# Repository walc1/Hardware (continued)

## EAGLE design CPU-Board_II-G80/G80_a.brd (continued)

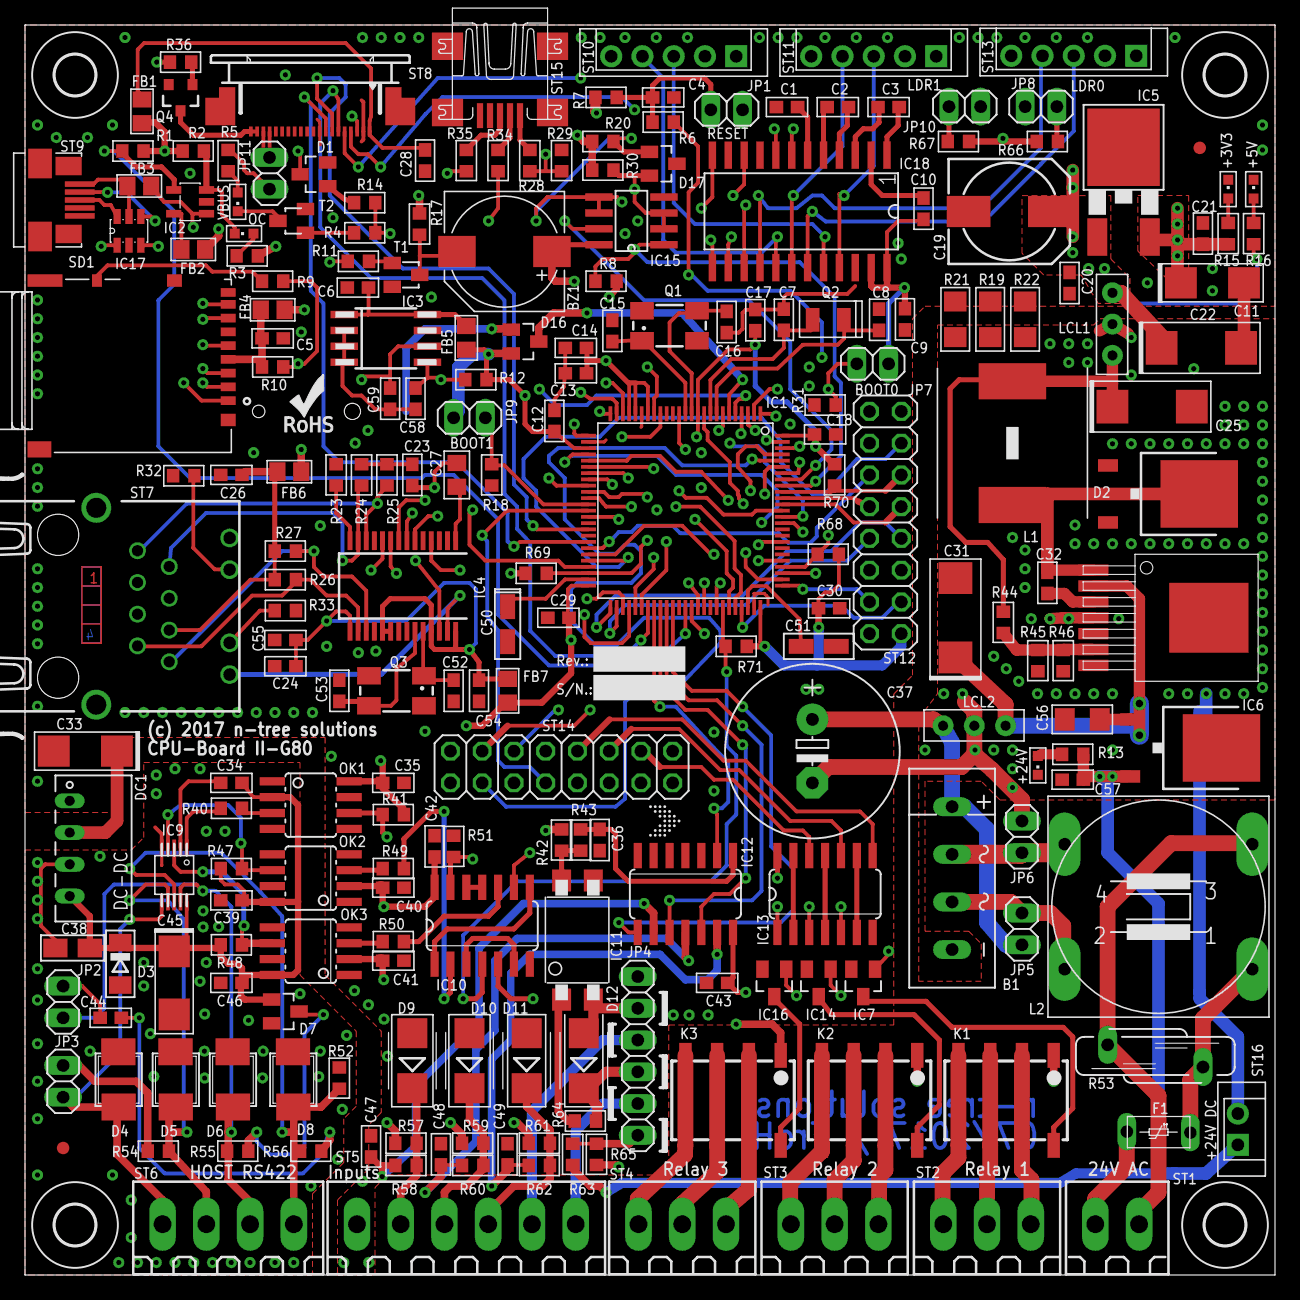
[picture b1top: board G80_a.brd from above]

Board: 4 copper layers, 100.0 x 100.0 mm, 227 parts (1 on the bottom side), 204 nets.

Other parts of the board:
U$1, U$2, U$3, U$4: 3,2

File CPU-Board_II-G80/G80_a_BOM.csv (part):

"Qty";"Value";"Device";"Package";"Parts";"Description";"AVAILABILITY";"DESCRIPTION";"MF";"MP";"MPN";"OC_FARNELL";"OC_NEWARK";"PACKAGE";"PRICE";"PROD_ID";"VALUE";
"7";"";"FERITTE-CHIP-BEAD";"R805";"FB1, FB2, FB3, FB4, FB5, FB6, FB7";"";"";"";"";"";"";"";"";"";"";"";"";
"1";"0,33uF/100V";"C-EUC1206";"C1206";"C56";"CAPACITOR, European symbol";"";"";"";"";"";"";"";"";"";"";"";
"2";"0R";"R-EU_R0603";"R0603";"R63, R65";"RESISTOR, European symbol";"";"";"";"";"";"";"";"";"";"";"";
"3";"0R";"R-EU_R1206";"R1206";"R19, R21, R22";"RESISTOR, European symbol";"";"";"";"";"";"";"";"";"";"";"";
"1";"1000uF/50V";"CPOL-EUE5-13";"E5-13";"C37";"POLARIZED CAPACITOR, European symbol";"";"";"";"";"";"";"";"";"";"";"";
"6";"100R";"R-EU_R0603";"R0603";"R6, R14, R36, R52, R54, R56";"RESISTOR, European symbol";"";"";"";"";"";"";"";"";"";"";"";
"2";"100k";"R-EU_R0603";"R0603";"R7, R55";"RESISTOR, European symbol";"";"";"";"";"";"";"";"";"";"";"";
"36";"100nF";"C-EUC0603";"C0603";"C1, C2, C3, C4, C5, C6, C9, C10, C12, C13, C14, C17, C18, C20, C21, C23, C24, C26, C28, C29, C30, C34, C35, C36, C39, C40, C41, C42, C43, C46, C47, C48, C49, C54, C55, C57";"CAPACITOR, European symbol";"";"";"";"";"";"";"";"";"";"";"";
"2";"100uF/16V lowESR";"CPOL-EUD/7343-31R";"D/7343-31R";"C22, C25";"POLARIZED CAPACITOR, European symbol";"";"";"";"";"";"";"";"";"";"";"";
"25";"10k";"R-EU_R0603";"R0603";"R1, R4, R10, R11, R17, R18, R28, R29, R31, R42, R43, R45, R51, R57, R58, R59, R60, R61, R62, R66, R67, R68, R69, R70, R71";"RESISTOR, European symbol";"";"";"";"";"";"";"";"";"";"";"";
"1";"10nF/100V";"C-EUC0603";"C0603";"C32";"CAPACITOR, European symbol";"";"";"";"";"";"";"";"";"";"";"";
"1";"10nF/50V";"C-EUC0603";"C0603";"C44";"CAPACITOR, European symbol";"";"";"";"";"";"";"";"";"";"";"";
"1";"10uF";"CPOL-EUC/6032-28R";"C/6032-28R";"C11";"POLARIZED CAPACITOR, European symbol";"";"";"";"";"";"";"";"";"";"";"";
"1";"10uF, GRM21BC81E106KE5L";"C-EUC0805";"C0805";"C27";"CAPACITOR, European symbol";"";"";"";"";"";"";"";"";"";"";"";
"2";"10uF/16V";"CPOL-EUC/6032-28R";"C/6032-28R";"C33, C45";"POLARIZED CAPACITOR, European symbol";"";"";"";"";"";"";"";"";"";"";"";
"2";"12,5pF";"C-EUC0603";"C0603";"C7, C8";"CAPACITOR, European symbol";"";"";"";"";"";"";"";"";"";"";"";
"1";"12MHz";"CRYSTALCTS406";"CTS406";"Q1";"CRYSTAL";"";"";"";"";"";"unknown";"unknown";"";"";"";"";
"1";"15µH 5A";"WE-PD_L/XL/XXL";"WE-PD_L/XL/XXL";"L1";"SMD-Shielded Power Inductors WE-PD";"";"";"";"";"";"";"";"";"";"";"";
"4";"18pF";"C-EUC0603";"C0603";"C15, C16, C52, C53";"CAPACITOR, European symbol";"";"";"";"";"";"";"";"";"";"";"";
"3";"1K5";"R-EU_R0603";"R0603";"R41, R47, R48";"RESISTOR, European symbol";"";"";"";"";"";"";"";"";"";"";"";
"2";"1k";"R-EU_R0603";"R0603";"R8, R12";"RESISTOR, European symbol";"";"";"";"";"";"";"";"";"";"";"";
"1";"1k2";"R-EU_R0603";"R0603";"R64";"RESISTOR, European symbol";"";"";"";"";"";"";"";"";"";"";"";
"1";"1uF/16V";"CPOL-EUA/3216-18R";"A/3216-18R";"C38";"POLARIZED CAPACITOR, European symbol";"";"";"";"";"";"";"";"";"";"";"";
"2";"2,2uF";"CPOL-EUCT3216";"CT3216";"C50, C51";"POLARIZED CAPACITOR, European symbol";"";"";"";"";"";"";"";"";"";"";"";
"1";"2,32k";"R-EU_R0603";"R0603";"R23";"RESISTOR, European symbol";"";"";"";"";"";"";"";"";"";"";"";
"1";"220R";"R-EU_R0603";"R0603";"R15";"RESISTOR, European symbol";"";"";"";"";"";"";"";"";"";"";"";
"2";"220pF";"C-EUC0603";"C0603";"C58, C59";"CAPACITOR, European symbol";"";"";"";"";"";"";"";"";"";"";"";
"1";"220uF/35V";"CPOL-EU150CLZ-0810";"150CLZ-0810";"C19";"POLARIZED CAPACITOR, European symbol";"";"";"";"";"";"";"";"";"";"";"";
"1";"24AA025E48";"24AA01SM";"SO-08M";"IC3";"Serial EEPROM";"";"";"MICROCHIP";"";"24AA01-I/SN";"1331268";"92C6793";"";"";"";"";
"1";"25MHz";"CRYSTALCTS406";"CTS406";"Q3";"CRYSTAL";"";"";"";"";"";"unknown";"unknown";"";"";"";"";
"2";"270R";"R-EU_R0603";"R0603";"R32, R33";"RESISTOR, European symbol";"";"";"";"";"";"";"";"";"";"";"";
"1";"2A";"RXEF0252";"RXEF025-2";"F1";"";"";"";"";"";"";"";"";"";"";"";"";
"1";"2KBP02M";"2KBP";"2KBP";"B1";"RECTIFIER";"";"";"";"";"";"";"";"";"";"";"";
"2";"2k2";"R-EU_R0603";"R0603";"R5, R44";"RESISTOR, European symbol";"";"";"";"";"";"";"";"";"";"";"";
"1";"32.768kHz";"CRYSTALS-NOGND-CFPX-217";"3.2X1.5-2-PAD";"Q2";"CRYSTALS CAN NOT GROUNDED";"";"";"";"";"";"";"";"";"";"";"";
"3";"330R";"R-EU_R0603";"R0603";"R9, R20, R30";"RESISTOR, European symbol";"";"";"";"";"";"";"";"";"";"";"";
"2";"33R";"R-EU_R0603";"R0603";"R34, R35";"RESISTOR, European symbol";"";"";"";"";"";"";"";"";"";"";"";
"1";"4,7µF lowESR 50V";"CPOL-EUD/7343-31R";"D/7343-31R";"C31";"POLARIZED CAPACITOR, European symbol";"";"";"";"";"";"";"";"";"";"";"";
"5";"470R";"R-EU_R0603";"R0603";"R13, R16, R40, R49, R50";"RESISTOR, European symbol";"";"";"";"";"";"";"";"";"";"";"";
"1";"47346-0001";"47346-0001";"MOLEX_47346-0001";"ST9";"CONN RCPT 5POS MICRO USB R/A  SMD";"Good";"Micro-USB%20B%20Receptacle%20with%20Flange%2C%20Bottom%20Mount%2C%20SMT%2C%20Lead-Free";"Molex";"47346-0001";"";"";"";"None";"0.54 USD";"";"";
"1";"47k";"R-EU_R0603";"R0603";"R2";"RESISTOR, European symbol";"";"";"";"";"";"";"";"";"";"";"";
"4";"49R9";"R-EU_R0603";"R0603";"R24, R25, R26, R27";"RESISTOR, European symbol";"";"";"";"";"";"";"";"";"";"";"";
"1";"4k7";"R-EU_R0603";"R0603";"R3";"RESISTOR, European symbol";"";"";"";"";"";"";"";"";"";"";"";
"1";"52745-2090";"52745-2090";"52745-2090";"ST8";"FFC/FPC-to-Board  0.50mm (.020") SMT Top Contact";"";"";"WALDOM/MOLEX";"";"52745-2090";"unknown";"38C9891";"";"";"";"";
"2";"6A,10N";"DSS6NZ82A103";"T-FILTERSIL";"LCL1, LCL2";"";"";"";"";"";"";"";"";"";"";"";"";
"3";"74HC14D";"74HC14D";"SO14";"IC10, IC12, IC13";"Hex schmitt trigger INVERTER";"";"";"";"";"";"";"";"";"";"";"";
"1";"7824DT";"7824DT";"TO252";"IC6";"Positive VOLTAGE REGULATOR";"";"";"";"";"";"";"";"";"";"";"";
"1";"820";"R-EU_R0603";"R0603";"R46";"RESISTOR, European symbol";"";"";"";"";"";"";"";"";"";"";"";
"2";"AC/DC";"PINHD-1X2";"1X02";"JP5, JP6";"PIN HEADER";"";"";"";"";"";"";"";"";"";"";"";
"1";"BAT54";"BAT54";"SOT23";"D1";"Schottky Diodes";"";"";"";"";"";"";"";"";"";"";"";
"1";"BAT54A";"BAT54A";"SOT23";"D17";"Schottky Diodes";"";"";"";"";"";"";"";"";"";"";"";
"1";"BAT54C";"BAT54C";"SOT23";"D16";"Schottky Diodes";"";"";"";"";"";"";"";"";"";"";"";
"1";"BAV99";"BAV99";"SOT23";"D7";"";"";"";"";"";"";"";"";"";"";"";"";
"1";"BC846";"BC846";"SOT23";"T1";"NPN TRANSISTOR";"";"";"";"";"";"";"";"";"";"";"";
"1";"BC846";"BC846-NPN-SOT23-BEC";"SOT23-BEC";"T2";"NPN Transistror";"";"";"";"";"";"";"";"";"";"";"";
"1";"BLV";"PINHD-1X2";"1X02";"JP11";"PIN HEADER";"";"";"";"";"";"";"";"";"";"";"";
"1";"BZV50C5V6";"ZENER-DIODESOD80C";"SOD80C";"D3";"Z-Diode";"";"";"";"";"";"";"";"";"";"";"";
"1";"Boot0";"PINHD-1X2";"1X02";"JP7";"PIN HEADER";"";"";"";"";"";"";"";"";"";"";"";
"1";"Boot1";"PINHD-1X2";"1X02";"JP9";"PIN HEADER";"";"";"";"";"";"";"";"";"";"";"";
"1";"CH291-1220LF";"CH291-1220LF";"CH291-1220LF";"BAT1";"Battery Holder, SMT, 12mm";"";"";"";"";"";"";"";"";"";"";"";
"1";"CMI-9655S-SMT";"KTG0905CL";"KTG0905CL";"BZ1";"";"";"";"";"";"";"";"";"";"";"";"";
"1";"COM2";"JST-EH5";"JST-EH5";"ST11";"Einbau-Stecker Fa. JST Typ EH 5pol, RM 2.5mm";"";"";"";"";"";"";"";"";"";"";"";
"1";"COM3";"JST-EH5";"JST-EH5";"ST10";"Einbau-Stecker Fa. JST Typ EH 5pol, RM 2.5mm";"";"";"";"";"";"";"";"";"";"";"";
"1";"COM4";"JST-EH5";"JST-EH5";"ST13";"Einbau-Stecker Fa. JST Typ EH 5pol, RM 2.5mm";"";"";"";"";"";"";"";"";"";"";"";
"1";"DM3AT-SF-PEJM5";"DM3AT-SF-PEJM5";"HRS_DM3AT-SF-PEJM5";"SD1";"DM3 Series 8 Position Right Angle SMT Push Push Ejection MicroSD Card Connector";"Good";"DM3%20Series%208%20Position%20Right%20Angle%20SMT%20Push%20Push%20Ejection%20MicroSD%20Card%20Connector";"Hirose";"DM3AT-SF-PEJM5";"";"";"";"None";"1.97 USD";"";"";
"1";"EN28J60SS";"EN28J60SS";"SSOP28";"IC4";"";"";"";"";"";"";"";"";"";"";"";"";
"1";"Extern 1";"PINHD-2X8";"2X08";"ST12";"PIN HEADER";"";"";"";"";"";"";"";"";"";"";"";
"1";"Extern 2";"PINHD-2X8";"2X08";"ST14";"PIN HEADER";"";"";"";"";"";"";"";"";"";"";"";
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
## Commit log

2017-04-16 First Init
2017-07-20 Set theme jekyll-theme-architect
2017-07-27 Add files via upload
    Inital Comit
2017-09-21 add to Git
2017-11-24 add auto test
2017-11-25 modify AutoTest
2017-11-26 add error log
2017-11-27 add ReaderTest
2018-01-16 add templates
2018-02-16 udp connection
2018-03-01 modify templates
2018-04-12 modify template and add firmware
2018-04-13 add new version
2018-04-19 add alive signal
2018-05-03 fix scroll function; add new firmware
2018-05-04 update firmware
2018-06-07 add new config and firmware
2018-07-11 ReaderTool Online alive signal
2018-07-12 add reader firmware
2018-07-12 add reader-tool light
2018-07-13 rename namespace
2018-07-13 minor
2018-07-13 rename
